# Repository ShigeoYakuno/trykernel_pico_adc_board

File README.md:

# 基板概要

## 全体

## 表面

## 裏面

## 3Dおもて

## 3D うら

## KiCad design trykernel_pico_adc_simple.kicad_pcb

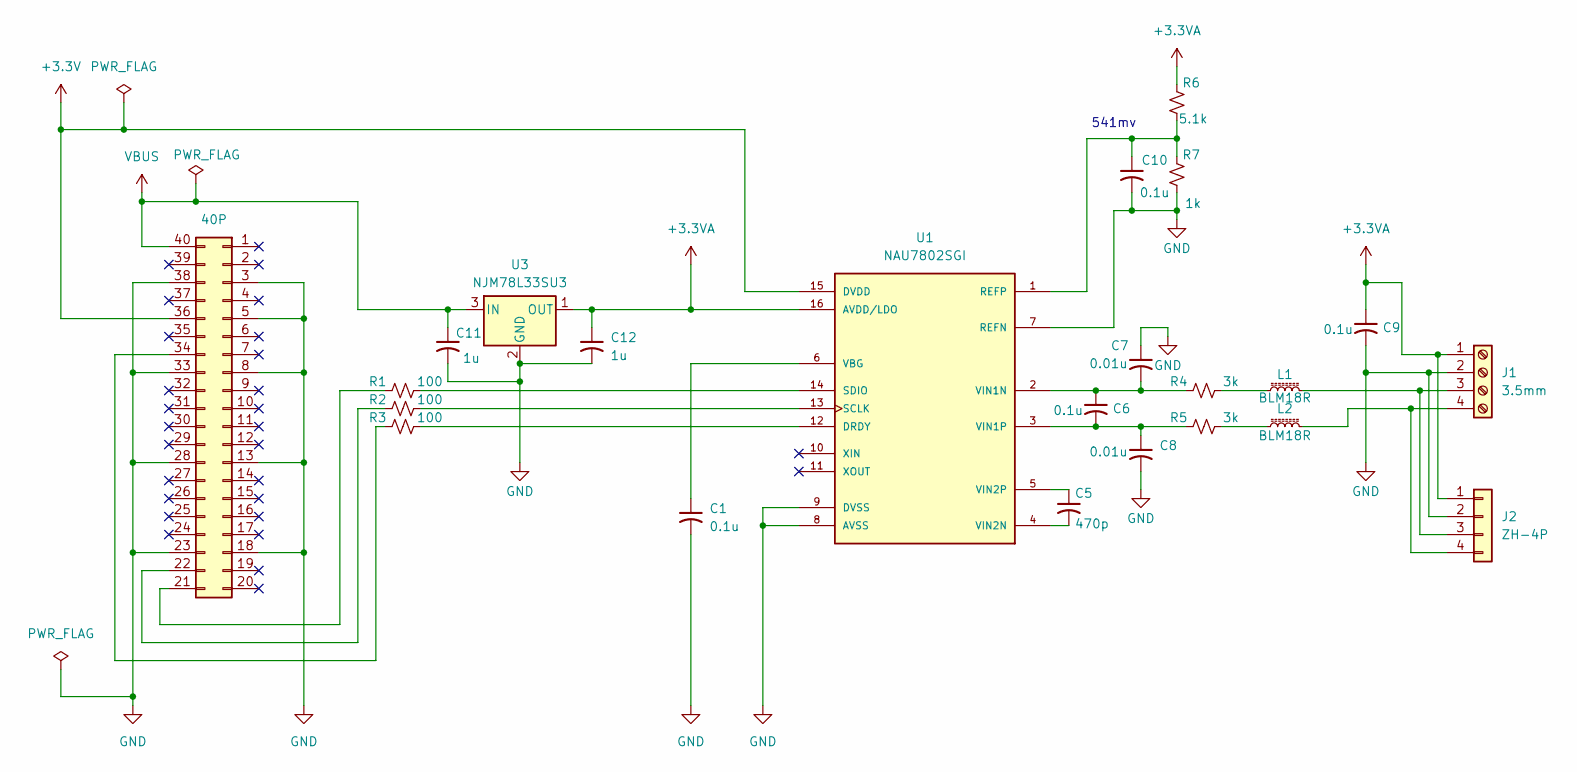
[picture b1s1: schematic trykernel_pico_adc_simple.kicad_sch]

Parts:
C1, C6, C9, C10: 0.1u; C_0603_1608Metric_Pad1.08x0.95mm_HandSolder
C5: 470p; C_0603_1608Metric_Pad1.08x0.95mm_HandSolder
C7, C8: 0.01u; C_0603_1608Metric_Pad1.08x0.95mm_HandSolder
C11, C12: 1u; C_0603_1608Metric_Pad1.08x0.95mm_HandSolder
J1: 3.5mm; TerminalBlock_4Ucon_1x04_P3.50mm_Horizontal
J2: ZH-4P; JST_ZH_B4B-ZR_1x04_P1.50mm_Vertical
J7: 40P; RPI_Hat_B+
L1, L2: BLM18R; R_0603_1608Metric_Pad0.98x0.95mm_HandSolder
R1, R2, R3: 100; R_0603_1608Metric_Pad0.98x0.95mm_HandSolder
R4, R5: 3k; R_0603_1608Metric_Pad0.98x0.95mm_HandSolder
R6: 5.1k; R_0603_1608Metric_Pad0.98x0.95mm_HandSolder
R7: 1k; R_0603_1608Metric_Pad0.98x0.95mm_HandSolder
U1: NAU7802SGI; SOIC127P600X175-16N; PARTREV 2.6
U3: NJM78L33SU3; SOT-89-3

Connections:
+3.3V: J7.36, U1.15 (DVDD)
+3.3VA: C9.1, C12.1, J1.1, J2.1, R6.2, U1.16 (AVDD/LDO), U3.1 (OUT)
GND: C1.2, C7.1, C8.2, C9.2, C10.2, C11.2, C12.2, J1.2, J2.2, J7.3, J7.5, J7.8, J7.13, J7.18, J7.23, J7.28, J7.33, J7.38, R7.1, U1.7 (REFN), U1.8 (AVSS), U1.9 (DVSS), U3.2 (GND)
unnamed: J1.3, J2.3, L1.2
unnamed: J1.4, J2.4, L2.2
unnamed: J7.21, R1.1
unnamed: J7.22, R2.1
unnamed: J7.34, R3.1
unnamed: L1.1, R4.2
unnamed: L2.1, R5.2
unnamed: R3.2, U1.12 (DRDY)
unnamed: C10.1, R6.1, R7.2, U1.1 (REFP)
unnamed: R2.2, U1.13 (SCLK)
unnamed: R1.2, U1.14 (SDIO)
unnamed: C1.1, U1.6 (VBG)
unnamed: C6.1, C7.2, R4.1, U1.2 (VIN1N)
unnamed: C6.2, C8.1, R5.1, U1.3 (VIN1P)
unnamed: C5.2, U1.4 (VIN2N)
unnamed: C5.1, U1.5 (VIN2P)
VBUS: C11.1, J7.40, U3.3 (IN)

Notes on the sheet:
541mv

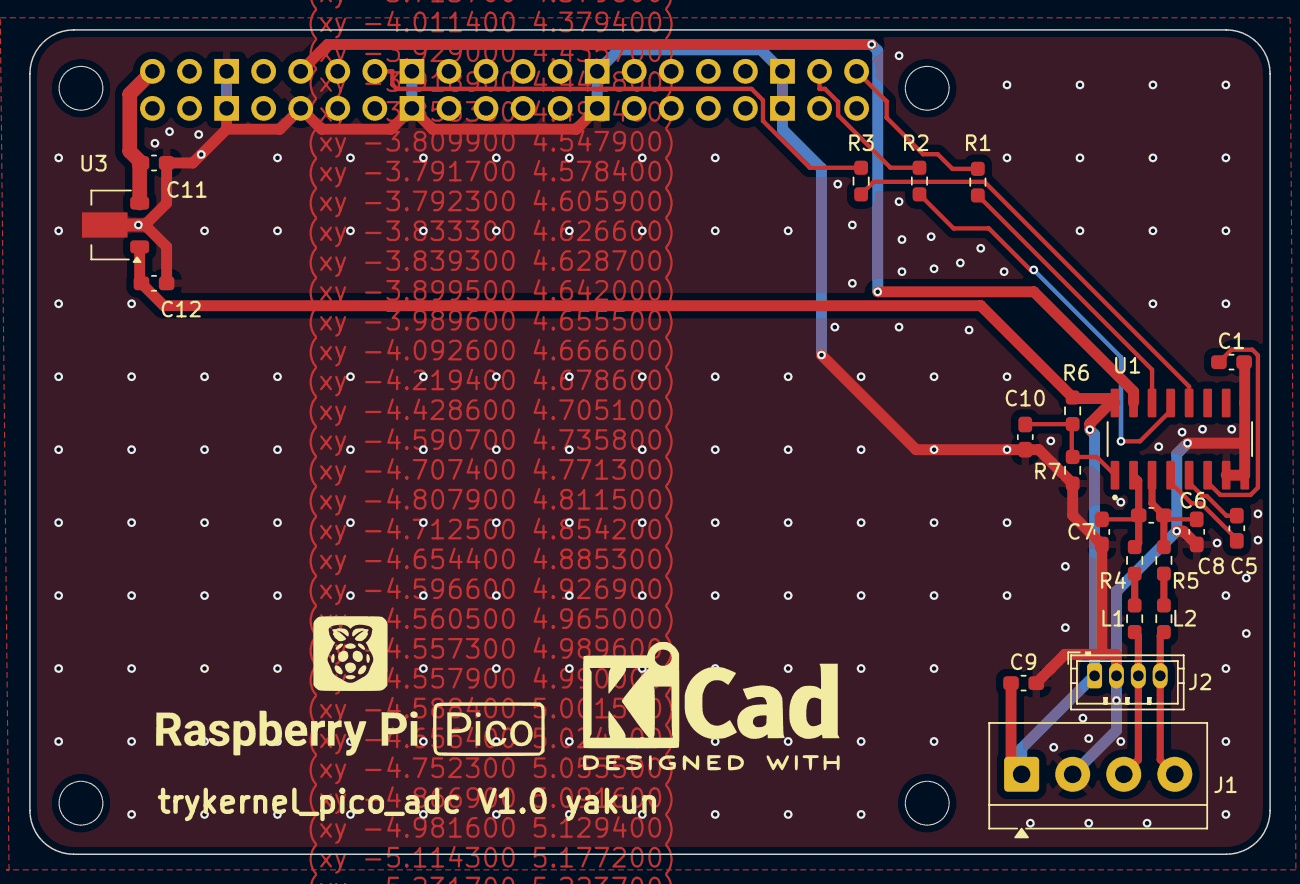
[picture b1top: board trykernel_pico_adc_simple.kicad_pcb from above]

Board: 2 copper layers, 85.0 x 56.5 mm, 23 parts (0 on the bottom side), 20 nets.

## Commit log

2025-05-14 version1.0 発注
